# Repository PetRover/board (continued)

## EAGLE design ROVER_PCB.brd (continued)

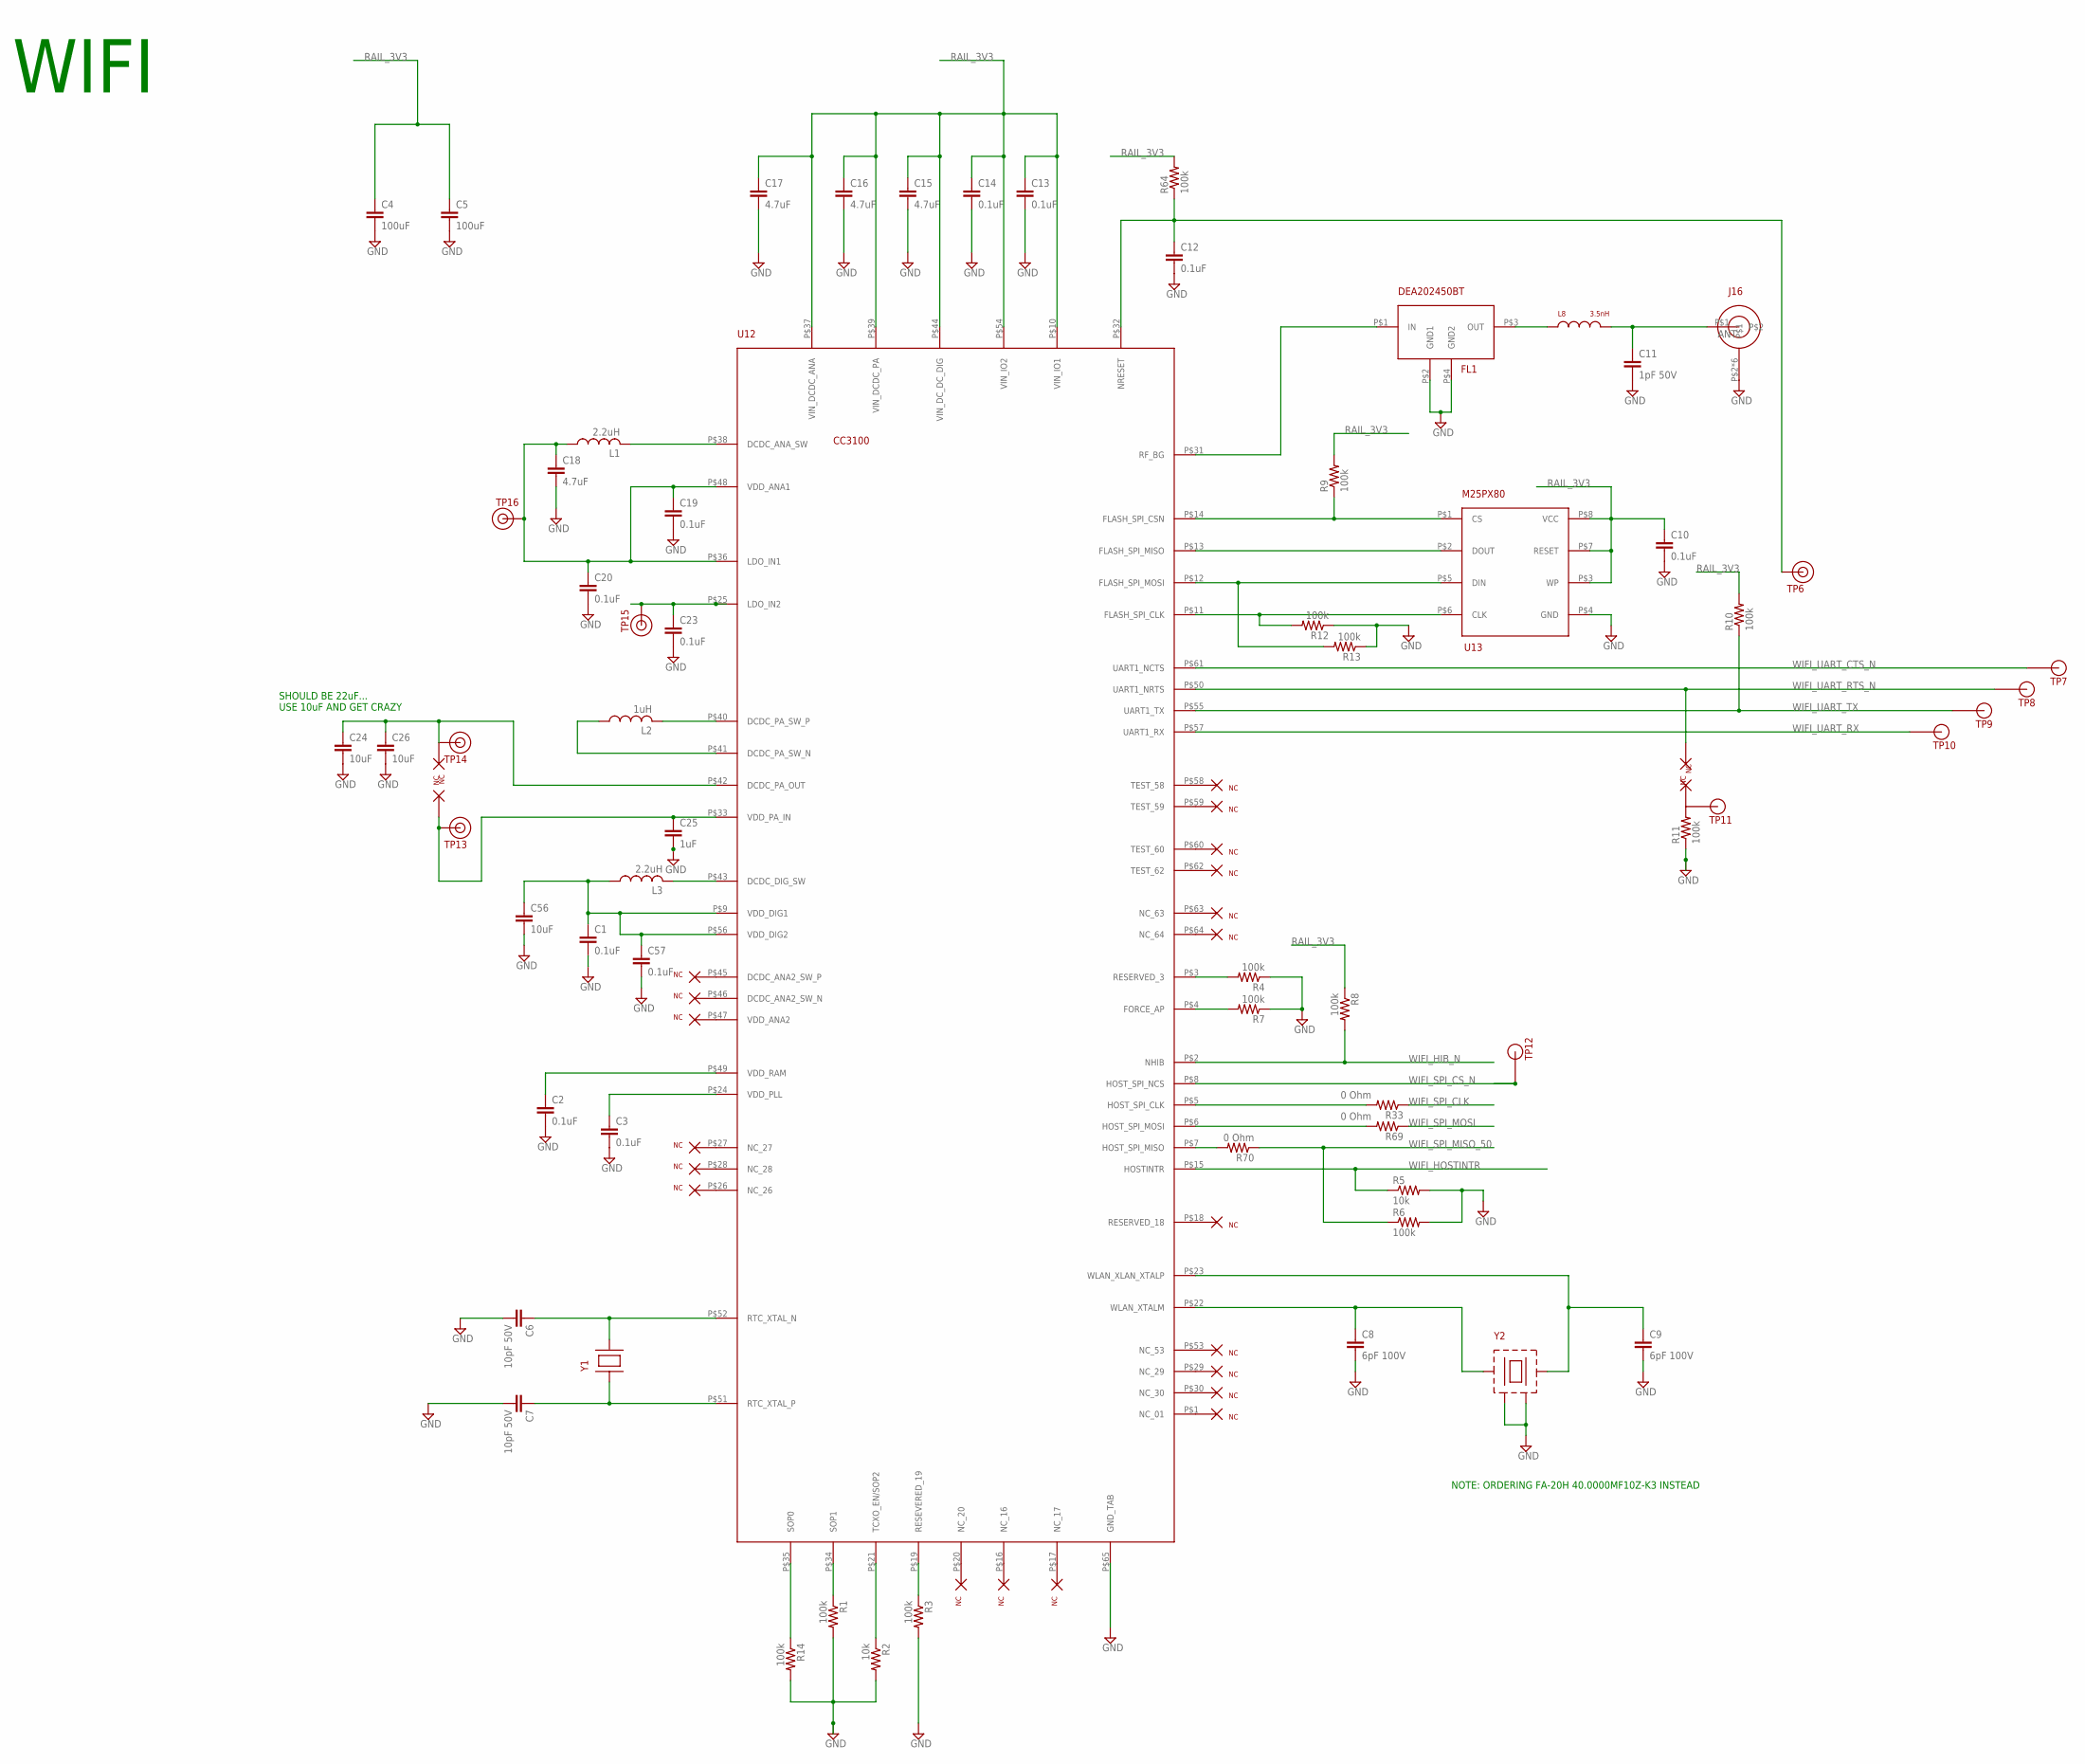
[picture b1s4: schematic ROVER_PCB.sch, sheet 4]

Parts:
C1, C3, C10, C12, C13, C14, C19, C20, C23, C57: 0.1uF; C0402
C2: 0.1uF; C0603
C4, C5: 100uF; C1206
C6, C7: 10pF 50V; C0402
C8, C9: 6pF 100V; C0402
C11: 1pF 50V; C0402
C15, C16, C17, C18: 4.7uF; C0402
C24, C26: 10uF; C0402
C25: 1uF; C0402
C56: 10uF; C0603
FL1: DEA202450BT
J16: SMA_CONNECTOR
L1, L3: 2.2uH; L1812
L2: 1uH; L1812
L8: 3.5nH; L0402
R1, R3, R4, R6, R7, R8, R9, R11, R12, R13, R14, R64: 100k; R0603
R2, R5: 10k; R0603
R10: 100k; R0402
R33, R69, R70: 0 Ohm; R0402
TP6, TP13, TP14, TP15, TP16: TEST_POINT
TP7, TP8, TP9, TP10, TP11, TP12: TP25MIL
U12: CC3100CORRECT_QFN; QFN64
U13: M25PX80; SO8N
Y1: ABS07-32.768KHZ-T
Y2: Q24FA20H00396

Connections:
ANT: C11.1, J16.P$1, L8.2
GND: C1.2, C2.2, C3.2, C4.2, C5.2, C6.2, C7.2, C8.2, C9.2, C10.2, C11.2, C12.2, C13.2, C14.2, C15.2, C16.2, C17.2, C18.2, C19.2, C20.2, C23.2, C24.2, C25.2, C26.2, C56.2, C57.2, FL1.P$2 (GND1), FL1.P$4 (GND2), J16.P$2, J16.P$3, J16.P$4, J16.P$5, J16.P$6, J16.P$7, R1.2, R2.2, R3.2, R4.1, R5.2, R6.2, R7.1, R11.1, R12.1, R13.1, R14.2, U12.P$65 (GND_TAB), U13.P$4 (GND), Y2.P$2, Y2.P$4; also elsewhere on the board
unnamed: C24.1, C26.1, TP14.P$1, U12.P$42 (DCDC_PA_OUT)
unnamed: C18.1, C19.1, C20.1, L1.1, TP16.P$1, U12.P$36 (LDO_IN1), U12.P$48 (VDD_ANA1)
unnamed: L3.2, U12.P$43 (DCDC_DIG_SW)
unnamed: C1.1, C56.1, C57.1, L3.1, U12.P$9 (VDD_DIG1), U12.P$56 (VDD_DIG2)
unnamed: C2.1, U12.P$49 (VDD_RAM)
unnamed: L1.2, U12.P$38 (DCDC_ANA_SW)
unnamed: L2.2, U12.P$40 (DCDC_PA_SW_P)
unnamed: L2.1, U12.P$41 (DCDC_PA_SW_N)
unnamed: C3.1, U12.P$24 (VDD_PLL)
unnamed: R14.1, U12.P$35 (SOP0)
unnamed: R1.1, U12.P$34 (SOP1)
unnamed: R2.1, U12.P$21 (TCXO_EN/SOP2)
unnamed: R3.1, U12.P$19 (RESEVERED_19)
unnamed: C8.1, U12.P$22 (WLAN_XTALM), Y2.P$1
unnamed: C9.1, U12.P$23 (WLAN_XLAN_XTALP), Y2.P$3
unnamed: C7.1, U12.P$51 (RTC_XTAL_P), Y1.P$1
unnamed: C6.1, U12.P$52 (RTC_XTAL_N), Y1.P$2
unnamed: R7.2, U12.P$4 (FORCE_AP)
unnamed: R4.2, U12.P$3 (RESERVED_3)
unnamed: R9.1, U12.P$14 (FLASH_SPI_CSN), U13.P$1 (CS)
unnamed: U12.P$13 (FLASH_SPI_MISO), U13.P$2 (DOUT)
unnamed: R13.2, U12.P$12 (FLASH_SPI_MOSI), U13.P$5 (DIN)
unnamed: R12.2, U12.P$11 (FLASH_SPI_CLK), U13.P$6 (CLK)
unnamed: FL1.P$1 (IN), U12.P$31 (RF_BG)
unnamed: FL1.P$3 (OUT), L8.1
unnamed: R11.2, TP11.P$1
unnamed: C25.1, TP13.P$1, U12.P$33 (VDD_PA_IN)
RAIL_3V3: C4.1, C5.1, C10.1, C13.1, C14.1, C15.1, C16.1, C17.1, R8.1, R9.2, R10.2, R64.2, U12.P$10 (VIN_IO1), U12.P$37 (VIN_DCDC_ANA), U12.P$39 (VIN_DCDC_PA), U12.P$44 (VIN_DC_DC_DIG), U12.P$54 (VIN_IO2), U13.P$3 (WP), U13.P$7 (RESET), U13.P$8 (VCC); also elsewhere on the board
U13: C23.1, TP15.P$1, U12.P$25 (LDO_IN2)
WIFI_HIB_N: R8.2, U12.P$2 (NHIB); also elsewhere on the board
WIFI_HOSTINTR: R5.1, U12.P$15 (HOSTINTR); also elsewhere on the board
WIFI_RESET_N_WIFI: C12.1, R64.1, TP6.P$1, U12.P$32 (NRESET)
WIFI_SPI_CLK: R33.1; also elsewhere on the board
WIFI_SPI_CLK_50: R33.2, U12.P$5 (HOST_SPI_CLK)
WIFI_SPI_CS_N: TP12.P$1, U12.P$8 (HOST_SPI_NCS); also elsewhere on the board
WIFI_SPI_MISO: R70.2, U12.P$7 (HOST_SPI_MISO)
WIFI_SPI_MISO_50: R6.1, R70.1; also elsewhere on the board
WIFI_SPI_MOSI: R69.1; also elsewhere on the board
WIFI_SPI_MOSI_50: R69.2, U12.P$6 (HOST_SPI_MOSI)
WIFI_UART_CTS_N: TP7.P$1, U12.P$61 (UART1_NCTS)
WIFI_UART_RTS_N: TP8.P$1, U12.P$50 (UART1_NRTS)
WIFI_UART_RX: TP10.P$1, U12.P$57 (UART1_RX)
WIFI_UART_TX: R10.1, TP9.P$1, U12.P$55 (UART1_TX)

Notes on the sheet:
WIFI
SHOULD BE 22uF... USE 10uF AND GET CRAZY
NOTE: ORDERING FA-20H 40.0000MF10Z-K3 INSTEAD

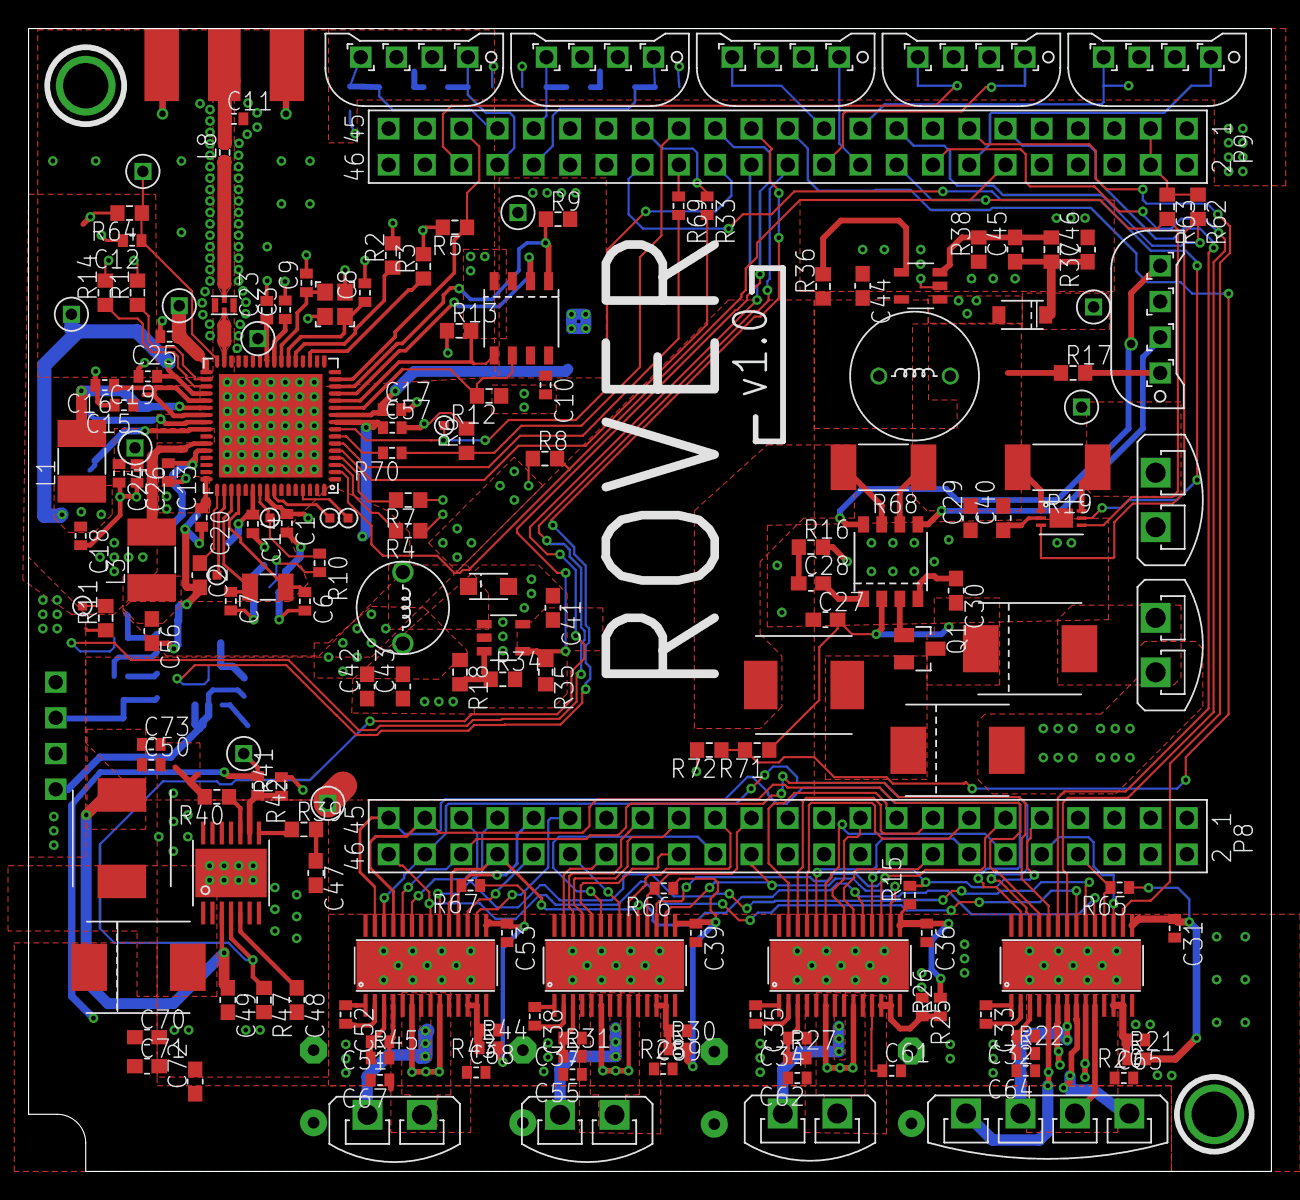
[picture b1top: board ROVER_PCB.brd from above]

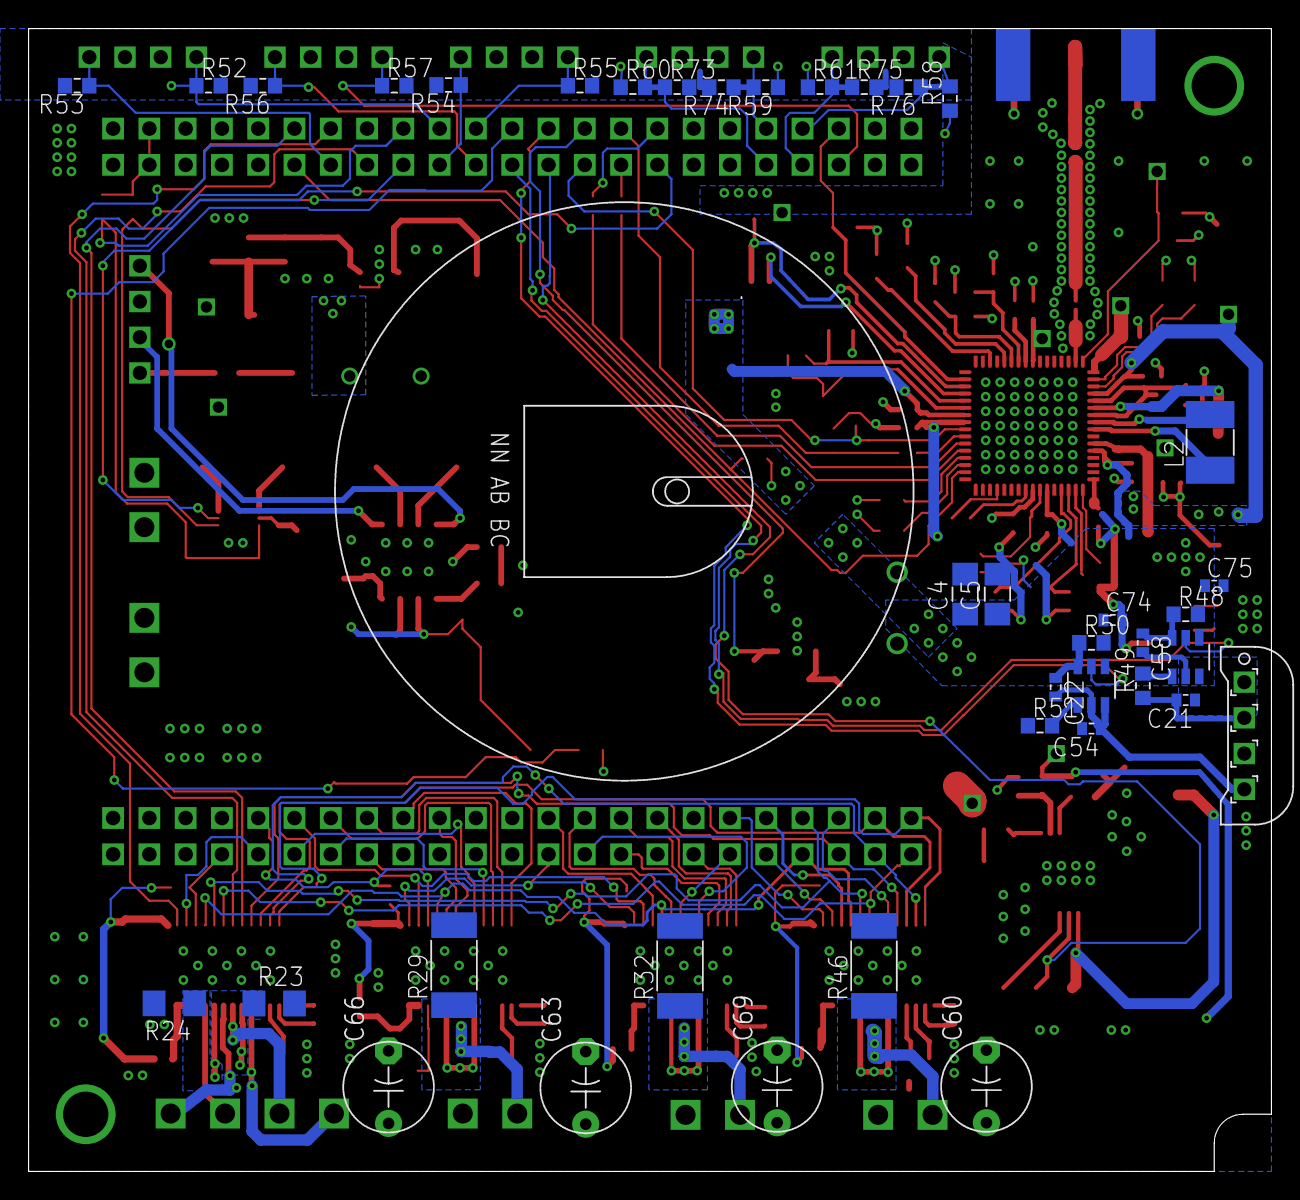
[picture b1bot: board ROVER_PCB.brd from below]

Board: 2 copper layers, 87.0 x 80.0 mm, 212 parts (39 on the bottom side), 164 nets.

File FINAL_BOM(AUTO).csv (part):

RPN,Description,Package,Value,Qty,State,Parts,Link,Device,DigikeyPN,MfgPN,Order Quant.
200-001,CAPACITOR,C0402,0.1uF,10,MATCHED,"C1, C3, C10, C12, C13, C14, C19, C20, C23, C57",http://www.digikey.com/product-detail/en/LMK105BJ104KV-F/587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,C-EUC0402,587-1227-1-ND,LMK105BJ104KV-F,50
200-002,CAPACITOR,C0603,0.1uF,3,MATCHED,"C2, C40, C47",https://www.digikey.com/product-detail/en/C0603C104K8RACTU/3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,C-EUC0603,399-1095-1-ND,C0603C104K8RACTU,50
200-003,CAPACITOR,C0402,0.1uF 16V,4,MATCHED,"C32, C34, C37, C51",https://www.digikey.com/product-detail/en/CC0402KRX7R7BB104/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,C-EUC0402,311-1338-1-ND,CC0402KRX7R7BB104,25
200-004,CAPACITOR,C0402,0.1uF 25V,8,MATCHED,"C55, C59, C61, C62, C64, C65, C67, C68",http://www.digikey.com/product-detail/en/GRM155R61E105KA12D/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,C-EUC0402,490-10017-1-ND,GRM155R61E105KA12D,50
200-005,CAPACITOR,C0603,0.1uF 25V,1,MATCHED,C27,http://www.digikey.com/product-detail/en/GRM188R71E104KA01D/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,C-EUC0603,490-1524-1-ND,GRM188R71E104KA01D,10
200-006,CAPACITOR,C0402,0.01uF 50V,4,MATCHED,"C33, C35, C38, C52",https://www.digikey.com/product-detail/en/C0402C103K5RACTU/3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,C-EUC0402,399-3066-1-ND,C0402C103K5RACTU,25
200-007,CAPACITOR,C0402,0.47uF,4,MATCHED,"C31, C36, C39, C53",http://www.digikey.com/product-detail/en/C1005X5R0J474K050BB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,C-EUC0402,445-4996-1-ND,C1005X5R0J474K050BB,12
200-008,CAPACITOR,C0603,0.047uF 25V,1,MATCHED,C48,http://www.digikey.com/product-detail/en/06033C473KAT2A/478-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,C-EUC0603,478-1235-1-ND,06033C473KAT2A,3
200-009,CAPACITOR,C0603,0.47uF 50V,1,MATCHED,C28,http://www.digikey.com/product-detail/en/CL10F474ZB8NNNC/127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,C-EUC0603,1276-2377-1-ND,CL10F474ZB8NNNC,10
200-010,CAPACITOR,C1206,100uF,2,MATCHED,"C4, C5",http://www.digikey.com/product-detail/en/C3216X5R0J107M160AB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,C-EUC1206,445-6008-1-ND,C3216X5R0J107M160AB,3
200-011,CAPACITOR,C0402,10pF 50V,2,MATCHED,"C6, C7",http://www.digikey.com/product-detail/en/GRM1555C1H100FA01D/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,C-EUC0402,490-6186-1-ND,GRM1555C1H100FA01D,10
200-012,CAPACITOR,C0402,10uF,6,MATCHED,"C24, C26, C50, C73, C74, C75",http://www.digikey.com/product-detail/en/CL05A106MP5NUNC/127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,C-EUC0402,1276-1450-1-ND,CL05A106MP5NUNC,12
200-013,CAPACITOR,C0603,10uF,1,MATCHED,C56,http://www.digikey.com/product-detail/en/GRM188R60J106ME47D/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,C-EUC0603,490-3896-1-ND,GRM188R60J106ME47D,3
200-014,CAPACITOR,C0603,10uF 10V,1,MATCHED,C46,http://www.digikey.com/product-detail/en/GRM188R61A106ME69D/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,C-EUC0603,490-10475-1-ND,GRM188R61A106ME69D,3
200-015,CAPACITOR,C0603,10uF 25V,4,MATCHED,"C30, C70, C71, C72",http://www.digikey.com/product-detail/en/GRM188R61E106MA73D/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,C-EUC0603,490-7202-1-ND,GRM188R61E106MA73D,10
200-016,CAPACITOR,C0402,1pF 50V,1,MATCHED,C11,http://www.digikey.com/product-detail/en/GJM1555C1H1R0BB01D/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,C-EUC0402,490-6073-1-ND,GJM1555C1H1R0BB01D,3
200-017,CAPACITOR,C0402,1uF,1,MATCHED,C25,http://www.digikey.com/product-detail/en/GRM155R60J105KE19D/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,C-EUC0402,490-1320-1-ND,GRM155R60J105KE19D,10
200-018,CAPACITOR,C0603,2.2uF,1,MATCHED,C44,http://www.digikey.com/product-detail/en/CC0603KRX5R6BB225/3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,C-EUC0603,311-1451-1-ND,CC0603KRX5R6BB225,3
200-019,CAPACITOR,C0603,220pF 50V,1,MATCHED,C45,http://www.digikey.com/product-detail/en/06035A221JAT2A/478-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,C-EUC0603,478-1179-1-ND,06035A221JAT2A,3
200-020,POLARIZED CAPACITOR,E5-6,220uF,4,MATCHED,"C60, C63, C66, C69",http://www.digikey.com/product-detail/en/EEU-FR1C221B/P15337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,CPOL-EUE5-6,P15337CT-ND,EEU-FR1C221B,6
200-021,CAPACITOR,C0603,22uF,5,MATCHED,"C29, C41, C42, C43, C49",http://www.digikey.com/product-detail/en/CC0603MRX5R5BB226/3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,C-EUC0603,311-1815-1-ND,CC0603MRX5R5BB226,10
200-022,CAPACITOR,C0402,4.7uF,4,MATCHED,"C15, C16, C17, C18",http://www.digikey.com/product-detail/en/CL05A475MQ5NRNC/127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,C-EUC0402,1276-1056-1-ND,CL05A475MQ5NRNC,12
200-023,CAPACITOR,C0402,6pF 100V,2,MATCHED,"C8, C9",http://www.digikey.com/product-detail/en/CBR04C609B1GAC/399-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,C-EUC0402,399-8610-1-ND,CBR04C609B1GAC,6
200-025,DIODE,B540C,B540C,3,MATCHED,"D3, D4, D5",http://www.digikey.com/product-detail/en/B540C-13-F/B540C-FD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,B540C,B540C-FDICT-ND,B540C-13-F,5
200-026,DIODE,CRS08,CRS08,1,MATCHED,D1,"http://www.digikey.com/product-detail/en/CRS08(TE85L,Q,M)/CRS08QMCT-ND/871562",CRS08,CRS08QMCT-ND,"CRS08(TE85L,Q,M)",2
200-027,DIODE,MBR05XX,MBR0520,1,MATCHED,D2,http://www.digikey.com/product-detail/en/MBR0520L-TP/MBR0520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,MBR0520,MBR0520L-TPMSCT-ND,MBR0520L-TP,2
200-028,SENSE RESISTOR,R2512,100mOhm,1,MANUAL,EXTERNAL,http://www.digikey.com/product-detail/en/1622825-9/A103652CT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,NONE,A103652CT-ND,1622825-9,1
200-029,SENSE RESISTOR,R2512,10mOhm,1,MANUAL,EXTERNAL,http://www.digikey.com/product-detail/en/LRMAM2512-R01FT4/98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,NONE,985-1553-1-ND,LRMAM2512-R01FT4,1
200-030,SENSE RESISTOR,R2512,1mOhm,1,MANUAL,EXTERNAL,http://www.digikey.com/product-detail/en/CRE2512-FZ-R001E-2/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,NONE,CRE2512-FZ-R001E-2CT-ND,CRE2512-FZ-R001E-2,1
200-031,SENSE RESISTOR,R2512,200mOhm,1,MANUAL,EXTERNAL,http://www.digikey.com/product-detail/en/73L7R20J/73L7R20JCT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,NONE,73L7R20JCT-ND,73L7R20J,1
200-032,SENSE RESISTOR,R2512,25mOhm,1,MANUAL,EXTERNAL,http://www.digikey.com/product-detail/en/CRA2512-FZ-R025ELF/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,NONE,CRA2512-FZ-R025ELFCT-ND,CRA2512-FZ-R025ELF,1
200-033,SENSE RESISTOR,R2512,50mOhm,2,MANUAL,EXTERNAL,http://www.digikey.com/product-detail/en/LRMAM2512-R05FT4/98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,NONE,985-1555-1-ND,LRMAM2512-R05FT4,2
200-034,BARREL CONNECTOR,PANEL MOUNT,5A MAX,1,MANUAL,EXTERNAL,http://www.digikey.com/product-detail/en/PJ-038AH/CP-038AH-N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,NONE,CP-038AH-ND,PJ-038AH,1
200-035,FUSE HOLDER ,IN WIRE,5_20mm Fuses,2,MANUAL,EXTERNAL,http://www.digikey.com/product-detail/en/01500274Z/F1468-ND/29453,NONE,F1468-ND,01500274Z,2
200-036,IR PHOTO DIODE,THOUGH HOLE,940NM,6,MANUAL,EXTERNAL,http://www.digikey.com/product-detail/en/PD204-6B/1080-1139-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,NONE,1080-1139-ND,PD204-6B,6
200-037,IR LED,THROUGH HOLE,940NM,6,MANUAL,EXTERNAL,http://www.digikey.com/product-detail/en/OED-EL-1L2/67-1001-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,NONE,67-1001-ND,OED-EL-1L2,6
200-038,OST CONNECTOR,2PIN OST,FEMALE,5,MANUAL,EXTERNAL,http://www.digikey.com/product-detail/en/OSTTJ0231530/ED2875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,NONE,ED2875-ND,OSTTJ0231530,6
200-039,OST CONNECTOR,4PIN OST,FEMALE,1,MANUAL,EXTERNAL,http://www.digikey.com/product-detail/en/OSTTJ0431530/ED2877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,NONE,ED2877-ND,OSTTJ0431530,1
200-040,BAND PASS FILTER,DEA202450BT,DEA202450BT,1,MATCHED,FL1,http://www.digikey.com/product-detail/en/DEA202450BT-1294C1-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,DEA202450BT,445-172335-1-ND,DEA202450BT-1294C1-H,2
200-041,OST CONNECTOR,2PIN_OST_3251,2PIN_OST_3251,5,MATCHED,"J2, J4, J5, J7, J8",http://www.digikey.com/product-detail/en/OSTOQ023251/ED2808-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,2PIN_OST_3251,ED2808-ND,OSTOQ023251,5
200-043,OST CONNECTOR,4PIN_OST_3251,4PIN_OST_3251,1,MATCHED,J3,http://www.digikey.com/product-detail/en/OSTOQ043251/ED2810-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,4PIN_OST_3251,ED2810-ND,OSTOQ043251,1
200-045,SMA CONNECTOR,SMA_CONNECTOR,SMA_CONNECTOR,1,MATCHED,J16,http://www.digikey.com/product-detail/en/0732511150/WM5534-N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,SMA_CONNECTOR,WM5534-ND,732511150,1
200-046,INDUCTOR,ASPI-0630LR,10uH,2,MATCHED,"L6, L7",https://www.digikey.com/product-detail/en/ASPI-0630LR-100M-T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,ASPI-0630LR,ASPI-0630LR-100M-T15CT-ND,ASPI-0630LR-100M-T15,4
200-047,INDUCTOR,L1812,1uH,1,MATCHED,L2,http://www.digikey.com/product-detail/en/LQM2HPN1R0MJ0L/490-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,L-USL1812,490-6699-1-ND,LQM2HPN1R0MJ0L,2
200-048,INDUCTOR,B82144B2222K,2.2uH,1,MATCHED,L5,http://www.digikey.com/product-detail/en/B82144B2222K/495-67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,B82144B2222K,495-6758-1-ND,B82144B2222K,2
200-049,INDUCTOR,L1812,2.2uH,2,MATCHED,"L1, L3",http://www.digikey.com/product-detail/en/LQM2HPN2R2MG0L/490-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,L-USL1812,490-5114-1-ND,LQM2HPN2R2MG0L,4
200-050,INDCUTOR,L0402,3.5nH,1,MATCHED,L8,http://www.digikey.com/product-detail/en/LQP15MN3N6B02D/490-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,LQP15MN3N6B02D,490-6756-1-ND,LQP15MN3N6B02D,3
200-051,INDUCTOR,AIUR-03,33uH,1,MATCHED,L4,http://www.digikey.com/product-detail/en/AIUR-03-330K/AIUR-0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,AIUR-03-330K,AIUR-03-330K-ND,AIUR-03-330K,2
200-052,PFET,SOT23,AO3407A,1,MATCHED,Q1,http://www.digikey.com/product-detail/en/AO3407A/785-1006-1-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,AO3407A,785-1006-1-ND,AO3407A,2
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
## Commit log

2015-09-12 VC for schematic
2015-09-12 added lib file
2015-09-14 learning git, updated some issues
2015-09-15 fixed issue #9
2015-09-16 updated some footprints. added library file. initial brd.
2015-09-17 adding library and minor footprint updates
2015-09-17 fixed footprint for DRV8842 and added solder mask defined thermal pad
2015-09-17 updated cc3100 package
2015-09-17 rearranged brd file. about 85% of it routes.
2015-09-17 removed pins 32,58,71 on bbb and redistributed to nets removed from 3-7
2015-09-17 updated component placement
2015-09-18 motor drivers routed
2015-09-18 routed 12V reg
2015-09-19 routed 5v regulator and made a bunch of component footprint additions and imporvments
2015-09-20 routed
2015-09-20 charging systems and all regulators routed. All footprints are done with mechanical outlines
2015-09-21 began wifi routing
2015-09-21 worked on part placement around wifi chip
2015-09-22 fixed footprint of wifi chip
2015-09-22 added gitignore for backup
2015-09-22 updated BBB footprint with proper numbers, mirrored BBB to gnd side of brd. updated part placement around wifi chip
2015-09-23 wip commit
2015-09-23 adding bom
2015-09-24 wifi mostly routed
2015-09-24 First pass at resistor, capacitor, and inductor values/digikey links
2015-09-25 net names for BBB on schematic
2015-09-25 Added more nets
2015-09-28 everything placed... working on final signal traces
2015-09-28 more WIP routing
2015-09-29 More capacitors/resistors selected
2015-09-29 WIP routing commit
2015-09-29 more resistors/capacitors
2015-09-29 WIP routing
2015-09-30 trying to fix pour issue that alyssa is having
2015-10-02 0 airwires, added silkscreen
2015-10-03 gerbers generated
2015-10-04 OK2FAB check
2015-10-15 Forgot to press save - even more capacitors
2015-10-15 A few more capacitors
2015-10-15 more capacitors/indcutors
2015-10-16 A few more resistors...getting there
2015-10-16 BOMB
2015-10-16 Adding to schematic
2015-10-17 THE BOM IS (BASICALLY) DONE
2015-10-17 Fully updated schematic will all component values
2015-10-17 WIP commit before changing symbols
2015-10-17 Changed to all US cap symbols
2015-10-20 BOM working commit
2015-10-20 Added 1% to critical resistors for identifcation
2015-10-21 ready for final check
2015-10-28 final commit of board (parts order and board fabbed)
